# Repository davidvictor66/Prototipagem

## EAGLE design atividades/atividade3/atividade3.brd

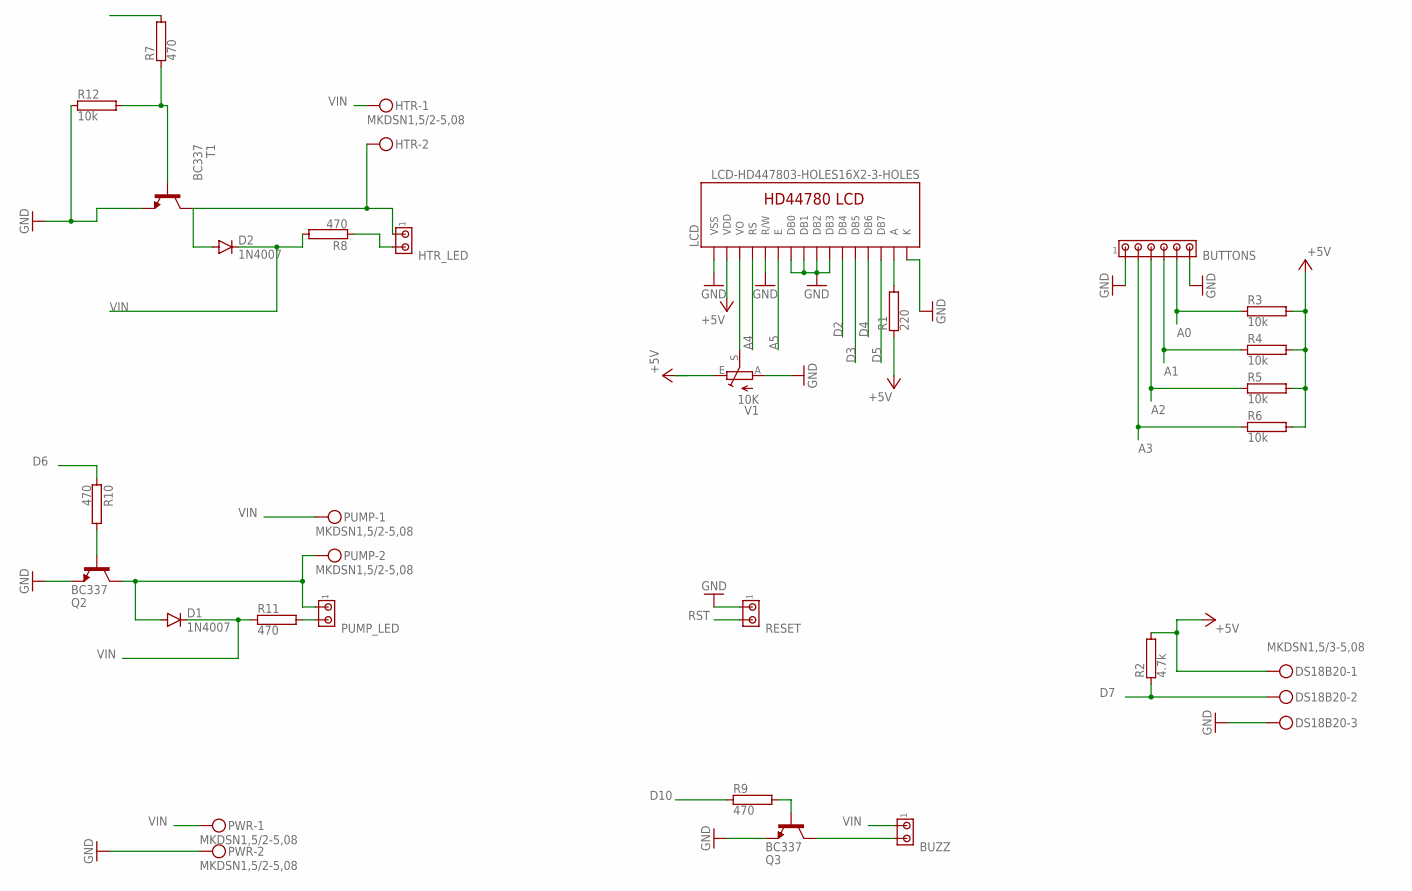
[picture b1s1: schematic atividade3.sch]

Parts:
BUTTONS: MTA06-100; 10X06MTA
BUZZ: MTA02-100; 10X02MTA
D1, D2: 1N4007; DO41-10
DS18B20: MKDSN1,5/3-5,08
HTR: MKDSN1,5/2-5,08
HTR_LED: MTA02-100; 10X02MTA
LCD: LCD-HD447803-HOLES16X2-3-HOLES; LCD-16X2-3HOLES
PUMP: MKDSN1,5/2-5,08
PUMP_LED: MTA02-100; 10X02MTA
PWR: MKDSN1,5/2-5,08
Q2, Q3: BC337; TO92
R1: 220; RS1/8
R2: 4.7k; RS1/8
R3, R4, R5, R6, R12: 10k; RS1/8
R7, R8, R9, R10, R11: 470; RS1/8
RESET: MTA02-100; 10X02MTA
T1: BC337; TO92
V1: 10K; B25P

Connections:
+5V: DS18B20.1, LCD.2 (VDD), R1.1, R2.2, R3.2, R4.2, R5.2, R6.2
+5V1: V1.E
A0: BUTTONS.5, R3.1
A1: BUTTONS.4, R4.1
A2: BUTTONS.3, R5.1
A3: BUTTONS.2, R6.1
A4: LCD.4 (RS)
A5: LCD.6 (E)
D2: LCD.11 (DB4)
D3: LCD.12 (DB5)
D4: LCD.13 (DB6)
D5: LCD.14 (DB7)
D6: R10.1
D7: DS18B20.2, R2.1
D9: R7.2
D10: R9.1
GND: BUTTONS.1, BUTTONS.6, DS18B20.3, LCD.1 (VSS), LCD.5 (R/W), LCD.7 (DB0), LCD.8 (DB1), LCD.9 (DB2), LCD.10 (DB3), LCD.16 (K), PWR.2, Q2.1 (E), Q3.1 (E), R12.1, RESET.1, T1.1 (E), V1.A
unnamed: R7.1, R12.2, T1.2 (B)
unnamed: D2.A, HTR.2, HTR_LED.1, T1.3 (C)
unnamed: D2.C, R8.2
unnamed: HTR_LED.2, R8.1
unnamed: Q2.2 (B), R10.2
unnamed: Q3.2 (B), R9.2
unnamed: LCD.15 (A), R1.2
unnamed: PUMP_LED.2, R11.2
unnamed: BUZZ.2, Q3.3 (C)
unnamed: LCD.3 (VO), V1.S
PUMP: D1.A, PUMP.2, PUMP_LED.1, Q2.3 (C)
RST: RESET.2
VIN: BUZZ.1, D1.C, HTR.1, PUMP.1, PWR.1, R11.1

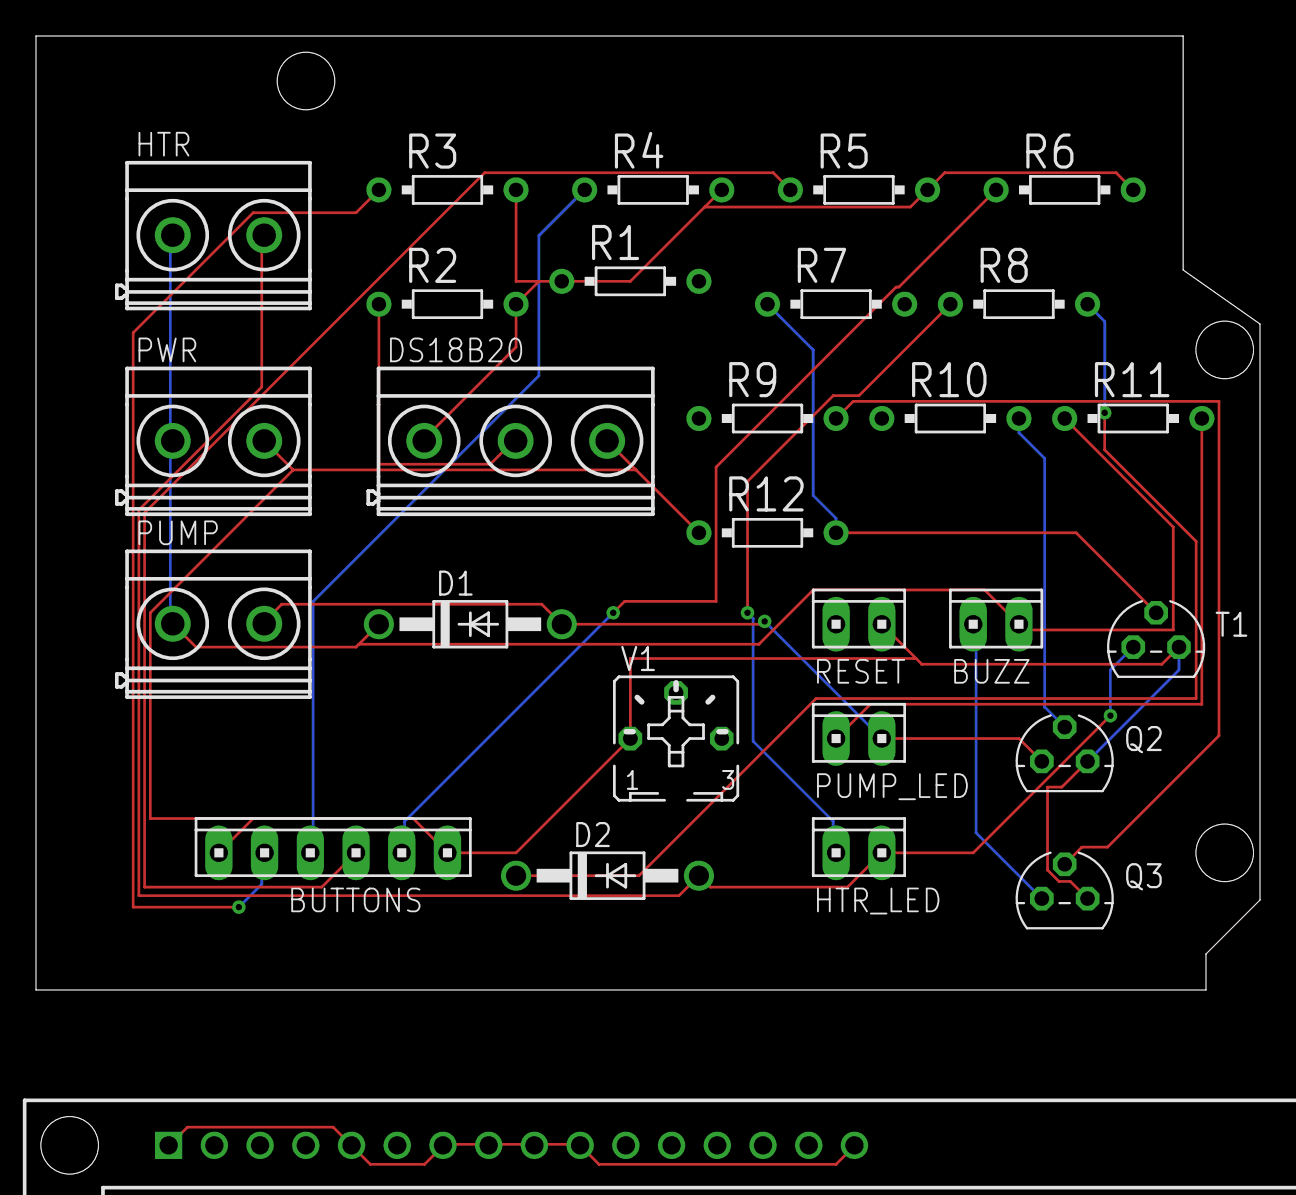
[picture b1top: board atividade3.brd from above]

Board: 2 copper layers, 68.0 x 53.0 mm, 28 parts (0 on the bottom side), 19 nets.
